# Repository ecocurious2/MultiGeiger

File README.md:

# MultiGeiger

Der MultiGeiger ist ein Messgerät für Radioaktivität. Er ist:

 * preiswert
 * ESP32-basiert
 * hat WiFi- bzw. WiFi/LoRa-Anbindung

**Multi**Geiger heißt er deshalb, weil das Gerät sehr viele Einsatz-Möglichkeiten hat:

 * Unterschiedliche Zählrohre - eine breite Palette von 400V-Zählrohren kann verwendet werden:

   - große Zählrohre, wie Si21g oder Si22g (wie wir es für die MultiGeiger-Messstation verwenden)
   - Mini-Zählrohr SBM21 (mit dem man sehr gut Hot-Spots aufspüren kann)

 * Unterschiedliche Verwendungen:

   - Multigeiger-Mess-Stationen für ein ODL-Mess-Netzwerk.
   - Mobiler Betrieb mit OLED-Anzeige.

# Ecocurious

Der MultiGeiger ist ein Projekt von Ecocurious, Deiner Umwelt-, Natur-  und Technik-Community, siehe https://ecocurious.de/projekte/multigeiger/.

Ziel ist es, ein Bürger-Messnetz für Radioaktivität in Deutschland aufzubauen.

Die MultiGeiger Hard- und Software hat Jürgen Böhringer konzipiert (http://www.boehri.de).

Reinhard/rexfue hat die Software und Platine weitergedacht und kümmert sich um die Einbindung der Sensoren in unsere Map https://ecocurious.de/multigeiger-karte/.

Wir haben die ersten Workshops gestartet, in denen Du die Bauteile und das Gehäuse mit unserer Unterstützung zusammenbauen kannst.

Workshop-Termine findest Du hier:
 * https://www.meetup.com/de-DE/Ecocurious-deine-Umwelt-Natur-und-Technik-Community/
 * https://ecocurious.de/events/

Klingt das interessant für Dich? Dann mach mit, herzliche Einladung!

## Installation
Hier in GitHub die neueste Release ( https://github.com/ecocurious/MultiGeiger/releases ) als Source code (zip) oder Source Code (tar.gz) herunterladen und entpacken.
Mit der Arduino-IDE in dem neuen Verzeichnis die Datei *multigeiger.ino* im Verzeichnis *multigeiger* öffnen.

Die Platine unterstützt zwei verschiedene Heltec-Bausteine, verschiedene Zählrohre und optional einen Temperatur/Luftdruck/Luftfeuchtigkeits-Sensor.
Die Software kann via Netzwerk Daten zu verschiedenen Services senden.

 * **Heltec WiFi Kit 32**
Diese MCU hat ein großes Display und WiFi.
Auf dem Board wird dieser Baustein in die längeren Buchsenleisten gesteckt.

 * **Heltec Wireless Stick**
Diese MCU hat ein sehr kleines Display, dafür aber zusätzlich zu WiFi noch LoRa.
Es wird in die kürzeren Buchsenleisten gesteckt.

Um die Heltec-Boards in der Arduino IDE auswählen zu können, muss https://raw.githubusercontent.com/espressif/arduino-esp32/gh-pages/package_esp32_dev_index.json in den Preferences unter Additional Boards Manager URLs hinzugefügt werden. Danach können unter Tools->Board->Boards Manager die ESP32 Boards (Name "esp32 by Espressif Systems")
installiert und anschließend unter Tools->Board das Heltec Board ausgewählt werden. Für **beide** Boards muss hier der **Heltec wireless Stick** ausgewählt werden. Die Software erkennt selbstständig, welches Board bestückt ist. Unter Tools muss noch **Flash size: "4MB(32Mb)"** und  **Partition Scheme: "Minimal SPIFFS (Large APPS with OTA)"** eingestellt werden.

Diverse Software-Einstellungen kann man über folgende Dateien machen (siehe Kommentare dort):

 * **./multigeiger/userdefines.h** (immer notwendig, ein Beispiel hierzu wird in userdefines-example.h mitgeliefert)
 * **./platformio.ini** (nur bei platformio, ein Beispiel hierzu wird in platformio-example.ini mitgeliefert)

Es werden alle externen Libraries benötigt, die in der Datei 
```
platformio-example.ini
```
unter dem Abschnitt 
```
lib-deps =
```
aufgelistet sind. Bitte jeweils die aktuellste Version über platform.io / Libraries installieren.

 **Achtung:** Wenn die Arduino-IDE verwendet wird, dann bitte prüfen, dass in der Datei project_config/lmic_project_config.h (in der obersten Ebene in dieser Library) unbedingt
```
die richtigen Configs eingestellt sind. Die Datei muss folgendermassen aussehen:
// project-specific definitions
#define CFG_eu868 1
//#define CFG_us915 1
//#define CFG_au921 1
//#define CFG_as923 1
// #define LMIC_COUNTRY_CODE LMIC_COUNTRY_CODE_JP	/* for as923-JP */
//#define CFG_in866 1
#define CFG_sx1276_radio 1
//#define LMIC_USE_INTERRUPTS
```
Die angegebenen Versionen der Libraries sind die Mindestanforderungen. Wir testen immer auch mit den neuesten Versionen, deshalb bitte immer die aktuellen Versionen installieren und verwenden.\
Falls der Compiler andere Libraries anmahnt, diese bitte in der Arduino IDE per *Sketch -> Include Library -> Manage Libraries ..* installieren.

## Ablauf nach dem Start
Das Gerät baut einen eigenen WLAN-Accesspoint (AP) auf. Die SSID des AP lautet **ESP32-xxxxxxxx**, wobei die xxx
die Chip-ID (bzw. die MAC-Adresse) des WLAN-Chips sind (Beispiel: **ESP32-51564452**).
**Bitte diese Nummer notieren, sie wird später noch gebraucht.**
Dieser Access-Point bleibt für 30sec aktiv. Danach versucht das Gerät, sich mit dem (früher) eingestellten WLAN
zu verbinden. Dieser Verbindungsversuch dauert ebenfalls 30sec. Kommt keine Verbindung zu Stande, wird wieder der
eigene AP für 30sec erzeugt. Wenn das WLAN nicht erreicht werden kann, läuft dieses Spiel endlos.
Solange keine Verbindung zum WLAN besteht, wird auf dem Display in der untersten Zeile ganz klein *connecting ...*
angezeigt. Diese Anzeige verschwindet, sobald eine WLAN-Verbindung hergestellt ist.

## Einstellung des WLAN
Wenn das Gerät den eigenen AP aufgebaut hat, verbindet man sich mit diesem. Entweder mit einem Handy oder einem PC o.ä..
Die Verbindung fragt nach einem Passwort, es lautet **ESP32Geiger**.
Ist die Verbindung mit dem Accesspoint hergestellt, hat man beliebig Zeit, die Daten einzugeben.
Es öffnet sich **automatisch** die Startseite des Gerätes. Es braucht also - in der Regel - nicht extra der Browser aufgerufen werden.
Falls die Startseite ausnahmsweise doch nicht erscheint, so muss mit dem Browser die Adresse **192.168.4.1** aufgerufen werden und nun erscheint die Startseite.
Dort findet man einen Link zur __configure page__ - dort drauf klicken und man kommt zur Einstellungsseite.

Diese hat die folgenden Zeilen:
 * Geiger accesspoint SSID\
 Dies ist die SSID des eingebauten APs und kann zwar geändert werden, sollte aber nicht! Der Sensor wird mit dieser Nummer bei sensor.community (früher: luftdaten.info) angemeldet. Wird sie geändert, muss eine neue Anmeldung erfolgen.
 * Geiger accesspoint password\
 Dies ist das Passwort für den eingebauten AP.\
 Dieses **MUSS** beim ersten Mal geändert werden. Es kann natürlich auch das gleiche Passwort **ESP32Geiger** wieder verwendet werden - wichtig ist nur, dass da was reingeschrieben wird und dass man das **nicht vergessen** darf.
 * WiFi client SSID\
 Hier muss die SSID des WLANs für den Netzwerk/Internet-Zugang eingegeben werden.
 * WiFi client password\
 Und hier das zugehörige Passwort.

Es wird empfohlen, beim WLAN das Gastnetz zu verwenden (falls ein solches existiert). Normalerweise wird das Gastnetz im Router vom normalen Netz abgeschottet und ist damit sicherer.

Ist alles eingegeben, kann man auf **Apply** drücken. Nun werden die eingestellten Daten übernommen und in das interne EEPROM gespeichert. Nun bitte **unbedingt** über **Abbrechen** diese Seite verlassen! Nur dann verlässt das Programm den Config-Mode und verbindet sich mit dem heimischen WLAN. Wenn es kein **Abbrechen** gibt, dann wieder zurück in die WLAN-Einstellungen des Gerätes gehen und da dann das normale Heim-Netzwerk wieder einstellen.

**ACHTUNG ACHTUNG**\
**Beim Update auf die Version 1.13 müssen die WLAN-Daten noch einmal neu eingegeben werden**. Bei zukünftigen Versionen wird das nicht mehr nötig sein.

Weiter können über die Einstell-Seite einige verschiedene Definitionen festgelegt werden:

* Start-Melodie, Lautsprecher-Tick, LED-Tick und Anzeige jeweils an oder aus
* Senden zu sensor.community oder/und zu madavi.de
* bei LoRa-Hardware können hier auch die LoRa-Kenngrößen (DEVEUI, APPEUI und APPKEY) eingegeben werden.

Am Ende der Einstellungsseite gibt es einen Link __Firmware update__ - hiermit kann man die Software auf dem MultiGeiger aktualisieren.
Man braucht dazu die .bin-Datei, wählt diese dann über **Browse...** aus und klickt zum Aktualisieren auf **Update**.
Danach dauert es ca. 30s für das Hochladen und Flashen der Datei.

Der Browser zeigt dann (hoffentlich) **Update Success! Rebooting...** an, der MultiGeiger startet dann neu und ab dann ist die neue
Firmware aktiv.

Erscheint **Update error: ...**, dann hat das Update nicht geklappt - es ist dann die seitherige Firmware weiter aktiv.

### Aufruf aus dem WLAN ###
Die Einstellseite kann zu jeder Zeit aus dem eigenen WLAN heraus aufgerufen werden. Dazu 
wird in der Adresszeile des Browsers http://esp32-xxxxxxx eingegeben. Hier ist xxxxxxx wieder die Chip-ID (siehe oben, Beispiel: **http://esp32-51564452**). Sollte es mit diesem Hostnamen nicht klappen, dann muss die IP-Adresse des Geigerzählers verwendet werden, diese kann aus dem Router ausgelesen werden.
Es erscheint zunächt eine Login-Seite.
Hier ist als Username **admin** und als Passwort das **Geiger accesspoint password** von oben einzugeben. Dann erscheint die gleiche Einstellseite wie oben beschrieben.

## Server
Es werden jeweils einen Messzyklus lang die Impulse gezählt und dann die "Counts per Minute" (cpm) berechnet.
Jeweils nach diesem Zyklus werden die Daten zu den Servern bei *sensor.community* und bei *madavi.de* gesendet.

Bei *sensor.community* werden die Daten gespeichert und stehen am nächsten Tag zum Abruf als CSV-Datei bereit:
http://archive.sensor.community/DATE/DATE_radiation_si22g_sensor_SID.csv
wobei DATE = Datum im Format YYYY-MM-DD ist (beides mal gleich) und SID die Sensornummer des Sensors (**nicht** die ChipID). Bei anderen Sensoren ist der Zählrohr-Name **si22g** durch den entsprechenden Namen zu ersetzen (z.B.: sbm-20 oder sbm-19) 

Bei *madavi* werden die Daten in einer RRD-Datenbank abgelegt und können direkt aktuell als Grafik über diesen Link betrachtet werden:
https://www.madavi.de/sensor/graph.php?sensor=esp32-CHIPID-si22g
Hier ist dann CHIPID die ChipId (also die Ziffern der SSID des internen Accesspoints).

Während der Übertragung der Daten zu den Servern wird in der Statuszeile (unterste Zeile) des Displays kurz der Name des Servers eingeblendet.

## Anmeldung bei sensor.community (luftdaten.info)
Damit die Daten, die der Sensor nach sensor.community schickt, von dem Server auch angenommen werden, muss man sich dort anmelden. Das geschieht über die Seite https://meine.luftdaten.info.
Zuerst über den *Registrieren*-Knopf einen Account anlegen. Dann damit über *Login* einloggen und *Neuen Sensor registrieren* anklicken.
Dann das Formular ausfüllen:
 * Erste Zeile, Sensor ID:\
 Hier die Nummer (nur die Zahlen) der SSID des Sensors eingeben (z.B. bei dem Sensor ESP-51564452 also dann nur 51564452 eingeben)
 * Zweite Zeile, Sensor Board:\
 Hier *esp32* auswählen (über die kleinen Pfeile rechts)
 * Basisinformation:\
 Hier die Adresse eingeben (mit dem Land!). Der interne Name des Sensors kann beliebig vergeben werden, muss aber eingegeben werden. Bitte den Haken bei **Indoor-Sensor** setzen, so lange der Sensor wirklich innen ist.
 * Zusätzliche Informationen:\
 Kann freigelassen werden, darf aber auch ausgefüllt werden.
 * Hardware-Konfiguration:\
 Hier als Sensor-Typ den Eintrag **Radiation Si22G** (oder ggf. entsprechend) auswählen. Für den zweiten Sensor kann DHT22 stehen bleiben, das ist für uns irrelevant.
 * Position\
 Hier bitte die Koordinaten eingeben, so genau wie möglich (oder über den rechten Knopf die Koordinaten rechnen lassen). Dies wird benötigt, um den Sensor später auf der Karte anzeigen zu können.

 Nun mit *Einstellungen speichern* das Ganze beenden. Dann auf der Übersichts-Seite bei diesem Sensor auf *Daten* klicken. Nun steht hinter *Sensor ID* die ID des Sensors. Diese bitte merken: sie wird für die Abfrage bei sensor.community bzw. bei der Anzeige auf https://multigeiger.citysensor.de benötigt.
 
## LoRa-Interface
Um den Multigeiger an TTN ("The Things Network") anzubinden, sind ein paar vorbereitende Schritte durchzuführen:

* Anlegen des TTN-Devices bei *The Things Network*
* Übernehmen der Parameter in den Multigeiger
* Anmelden bei *sensor.community* (ehemals luftdaten.info)
* HTTP-Integration

### Anlegen eines TTN-Devices
Das Gerät muss bei TTN (The Things Network) angemeldet werden. Dazu muss zuerst (falls noch nicht vorhanden) ein Account bei TTN angelegt werden.

#### Account anlegen
Über <https://account.thethingsnetwork.org/register> auf die Webseite zum Account anlegen gehen. Hier dann einen **USERNAME** vergeben, die **EMAIL ADRESSE** eintragen und auch ein **PASSWORD** vergeben. Dann rechts unten über **Create account** den Account anlegen. Danach kann man sich mit den neuen Daten an der Console anmelden (<https://account.thethingsnetwork.org/users/login>).

#### Applikation anlegen
Ist man eingelogged, wird über **APPLICATIONS** und **add applications** die neue Applikation angelegt. Folgende Felder müssen ausgefüllt werden:

* **Application ID:**\
Eine beliebige Bezeichnung für diese Applikation, die darf es aber in dem Netzwerk noch nicht geben (also z.B.: geiger_20200205)
* **Description:**\
Hier kann eine beliebige Beschreibung der Apllikation eingegeben werden.
* **Application EUI:**\
Bleibt frei, die Nummer wird vom TTN-System erzeugt.
* **Handler registration:**\
Der vorausgefüllte Wert (ttn-handler-eu) ist schon richtig und bleibt stehen.

Nun mit **Add application** rechts unten die Apllikation hinzufügen.

#### Device anlegen
Zuletzt muss noch das Device angelegt werden. Dazu in der Übersicht der Applikationen die gerade neu angelegte Applikation auswählen (klicken). Hier dann im mittleren Bereich bei **DEVICES** das Anlegen eines neuen Devices über **register device** starten. Folgende Felder müssen ausgefüllt werden:

* **Device ID:**\
Ein beliebiger Name für das Device. Er muss innerhalb der Applikation eindeutig sein (also z.B.: geiger_01) und nur aus Kleinbuchstaben bestehen.
* **Device EUI:**\
Einmal auf das Symbol ganz links an der Zeile klicken, dann erscheint der Text, dass diese Nummer vom System erzeugt wird. Wir müssen sonst nichts weiter eingeben.
* **App Key:**\
Keine Eingabe nötig
* **App EUI:**\
Bleibt so stehen

Nun rechts unten auf **Register**. Nun ist auch das Device angelegt.

### Übernahme der LoRa-Parameter 
Die LoRa-Parameter müssen noch in das Programm übernommen werden.\
Dazu muss die Konfigurations-Webseite des Geigerzählers aufgerufen werden. Weiter oben ist erklärt, wie die Konfigurations-Seite zu erreichen ist (*Einstellung des WLAN* und *Aufruf aus dem WLAN*))

Nun auf der Konfigurations-Seite durch die Konfiguration gehen bis die Einstellung der LoRa-Parameter angezeigt wird. Nun die 3 Werte (**APPEUI, DEVEUI, APPKEY**) aus der TTN-Console (siehe oben) entnehmen und hier dann eintragen. In der TTN-Console auf das Device gehen, das oben angelegt wurde. Hier sind die 3 Werte zu finden. Es müssen die HEX-Werte **ohne** Leerzeichen eingegeben werden, und zwar so, wie sie in der TTN-Console erscheinen.
Beispiel:\
in der TTN-Console steht

```
Device EUI  00 D0 C0 00 C3 19 7C E8
```
Dann muss folgendes eingeben werden:

```
00D0C000C3197CE8
```
Dies gilt genauso ebenso für die **APPEUI** und den **APPKEY** .

### Anmelden bei sensor.community (ehem. luftdaten.info)
Wenn der Multigeiger seine Daten über TTN auch an *sensor.community* weitergeben soll, muss er dort angemeldet werden.
Die Anmeldung ist ziemlich ähnlich wie oben schon beschrieben. Hier werden nur die Änderungen erläutert (gesamten Ablauf bitte oben nachlesen).

 * Sensor ID:\
 Hier den hinteren Teil der DEVEUI eingeben (wenn also - siehe oben - die DEVEUI *00 D0 C0 00 C3 19 7C E8* heißt, sind die hinteren 4 Byte ( also *C3197CE8*) in dezimal umgerechnet ( also hier 3273227496 ) einzugeben.
 * Sensor Board:\
 Hier **TTN** auswählen (über die kleinen Pfeile rechts).

### HTTP-Integration
Um die Daten von TTN an *sensor.community* zu bekommen, muss noch die HTTP-Integration bei TTN eingestellt werden.\
In der TTN-Console *Applications* anklicken und dann die Applikation des Geigerzählers (z.B. *geiger_20200205*) anklicken. Dann rechts oben in der Leiste mit *Overview*, *Devices*, *Payload Formats*, *Integrations*, *Data*, *Settings* das **Integrations** anklicken. Hier dann über **add integration** die **HTTP Integration** auswählen.

Nun die angezeigten Felder ausfüllen:\
 **Process ID:**\
 	Hier einen beliebigen Namen für diese Integration vergeben\
 **Access Key:**\
 	Hier einmal rein klicken und den *default key* auswählen\
 **URL:**\
 	Hier nun die URL zum ttn2luft-Programm eingeben: <https://ttn2luft.citysensor.de>\
 **Method:**\
 	da steht schon *POST*, das lassen\
 **Authorization:**\
 	bleibt leer\
 **Custom Header Name:**\
 	hier kommt der Text **X-SSID** rein\
 **Custom Header value:**\
 	und da dann die SSID des Sensors (also die Nummer, die man bei der Anmeldung bei sensor.community erhalten hat, *NICHT* die Chip-ID).

Dann rechts unten auf **Add integration** klicken. Das war's dann.\
Und so etwa sieht das dann ausgefüllt aus:\

### TTN-Payload (Beispiel)
Um in der TTN-Console nicht nur die Datenbytes sondern lesbare Werte zu sehen, kann ein kleines Script als payload-Decoder eingefügt werden.\
Auf der *The Things Network* Webseite einloggen, über **Applications** die oben angelegte Application suchen und dann anklicken. Hier in der Menü-Zeile den Tab **Payload Formats** auswählen. Dann den folgenden Code in das Feld einfügen (den vorhandenen Code überschreiben):

```
function Decoder(bytes, port) {
  // Decode an uplink message from a buffer
  // (array) of bytes to an object of fields.
  var decoded = {};
  if(port == 1) {
  decoded.counts = ((bytes[0]*256 + bytes[1]) * 256 + bytes[2]) * 256  + bytes[3];
  decoded.sample_time = (bytes[4] * 256 + bytes[5]) * 256 + bytes[6];
  decoded.tube = bytes[9];
  var minor = (bytes[7]&0xF)+(bytes[8]>>4) ;
  decoded.sw_version="" + (bytes[7]>>4) + "." + minor + "." + (bytes[8]&0xF);
  }
  if (port === 2) {
    decoded.temp = ((bytes[0] * 256 + bytes[1]) / 10) + "°C";
    decoded.humi = bytes[2] / 2 + "%";
    decoded.press = ((bytes[3] * 256 + bytes[4]) / 10) + "hPa";
  }
  return decoded;
}
```

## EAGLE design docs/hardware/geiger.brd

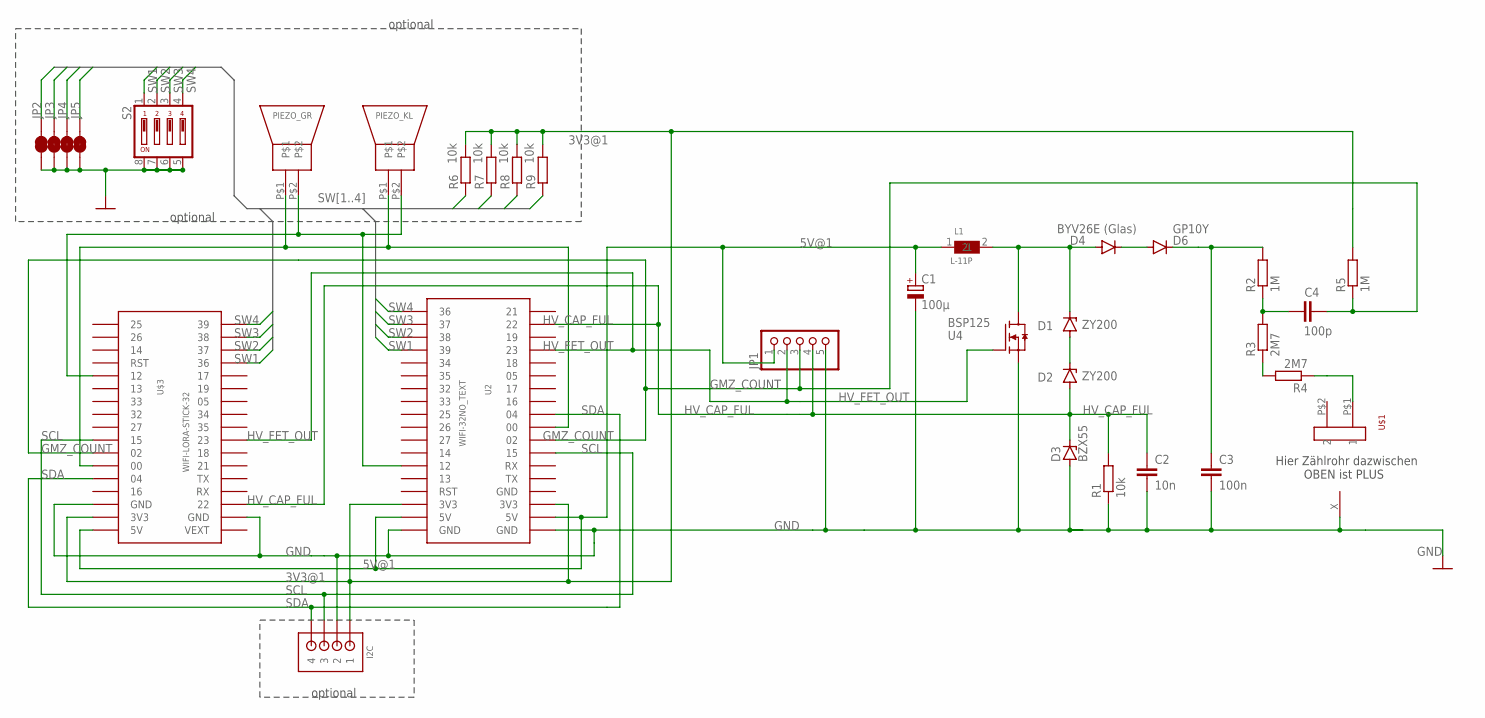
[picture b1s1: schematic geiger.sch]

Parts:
C1: 100µ; E2-5
C2: 10n; C050-035X075
C3: 100n; C150-072X183
C4: 100p; C050-045X075
D1, D2: ZY200; DO41Z10
D3: BZX55; DO35Z10
D4: BYV26E (Glas); DO41-10
D6: GP10Y; DO41-10
I2C: B4B-ZRSIDE_ENTRY; S4B-ZR
JP1: PINHD-1X5; 1X05
JP2: Jumper; SMT-JUMPER_2_NC_TRACE_NO-SILK
JP3, JP4, JP5: JUMPER-SMT_2_NC_TRACE_NO-SILK; SMT-JUMPER_2_NC_TRACE_NO-SILK
L1: L-11P
PIEZO_GR: PIEPSER_BIG
PIEZO_KL: PIEPSER
R1: 10k; 0207/10
R2, R5: 1M; 0207/10
R3, R4: 2M7; 0207/10
R6, R7, R8, R9: 10k; M0805
S2: DIP04YL
U2: WIFI-32NO_TEXT; 2.54MM_2X18_NOLORA_NOTEXT
U4: BSP125; SOT223
U$1: FUSE_HOLDER
U$3: WIFI-LORA-STICK-32; 2.54MM_2X18_STICK_NO_TEXT
U$5: ONE_PAD

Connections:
3V3@1: I2C.1, R5.2, R6.2, R7.2, R8.2, R9.2, U2.P$3 (3V3), U2.P$34 (3V3), U$3.P$33 (3V3)
5V@1: C1.+, JP1.1, L1.1, U2.P$2 (5V), U2.P$35 (5V), U$3.P$34 (5V)
GMZ_COUNT: C4.2, JP1.3, R5.1, U2.P$29 (02), U$3.P$28 (02)
GND: C1.-, C2.2, C3.2, D3.A, I2C.2, JP1.5, JP2.1, JP3.1, JP4.1, JP5.1, R1.1, S2.5, S2.6, S2.7, S2.8, U2.P$1 (GND), U2.P$36 (GND), U4.3 (S), U$3.P$2 (GND), U$3.P$32 (GND), U$5.X
HV_CAP_FUL: C2.1, D2.A, D3.C, JP1.4, R1.2, U2.P$20 (22), U$3.P$3 (22)
HV_FET_OUT: JP1.2, U2.P$22 (23), U4.1 (G), U$3.P$8 (23)
unnamed: D1.A, D2.C
unnamed: D1.C, D4.A, L1.2, U4.2 (D), U4.4 (D)
unnamed: C3.1, D6.C, R2.2
unnamed: R4.1, U$1.P$1 (1)
unnamed: R3.1, R4.2
unnamed: C4.1, R2.1, R3.2
unnamed: D4.C, D6.A
unnamed: PIEZO_GR.P$2, PIEZO_KL.P$2, U2.P$6 (12), U$3.P$22 (12)
unnamed: PIEZO_GR.P$1, PIEZO_KL.P$1, U2.P$28 (00), U$3.P$29 (00)
SCL: I2C.3, U2.P$30 (15), U$3.P$27 (15)
SDA: I2C.4, U2.P$27 (04), U$3.P$30 (04)
SW1: JP5.2, R6.1, S2.1, U2.P$15 (39), U$3.P$14 (36)
SW2: JP4.2, R7.1, S2.2, U2.P$16 (38), U$3.P$15 (37)
SW3: JP3.2, R8.1, S2.3, U2.P$17 (37), U$3.P$16 (38)
SW4: JP2.2, R9.1, S2.4, U2.P$18 (36), U$3.P$17 (39)

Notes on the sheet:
Hier Zählrohr dazwischen OBEN ist PLUS
optional

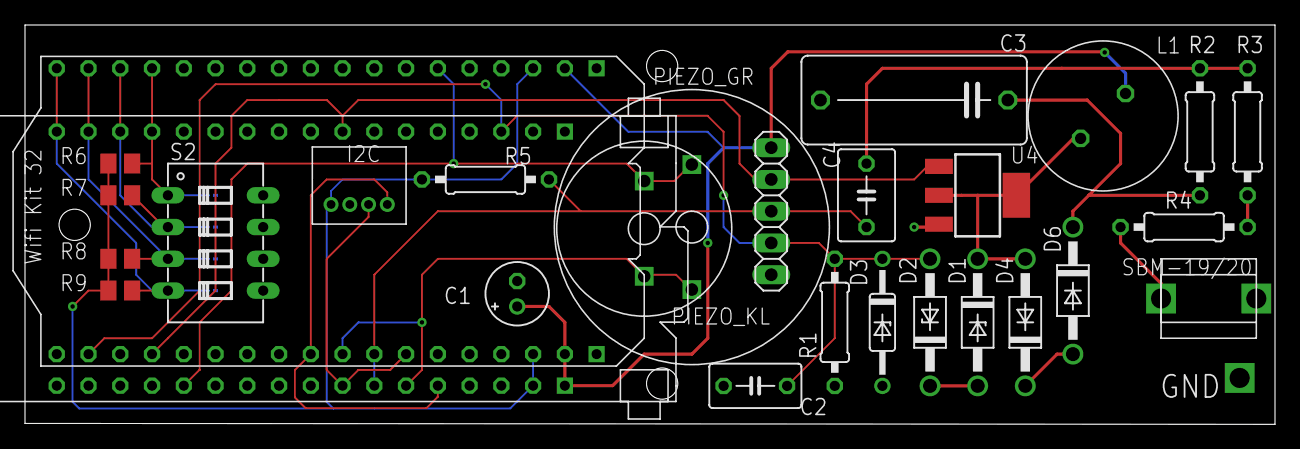
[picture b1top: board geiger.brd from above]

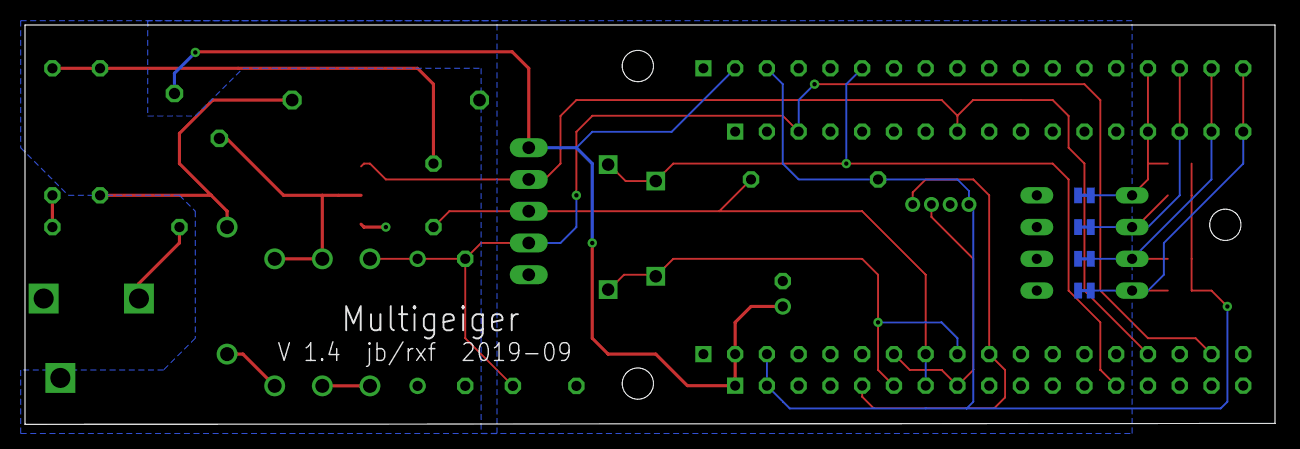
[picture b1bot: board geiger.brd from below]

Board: 2 copper layers, 100.0 x 31.9 mm, 33 parts (4 on the bottom side), 21 nets.

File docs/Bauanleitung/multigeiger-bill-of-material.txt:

TEIL	ANZAHL 	BESCHREIBUNG	Artikelbezeichnung	LINK
T1	1	N-MOS-Transistor BSP125,	BSP125H6433XTMA1	https://www.digikey.ch/product-detail/de/BSP125H6433XTMA1/BS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
R1	1	kOhm Widerstand, braun-schwarz-orange-gold, Kohleschicht, 0411, 500 mW, 5%	z.B. RD12JN103T52	https://www.reichelt.de/ch/de/widerstand-kohleschicht-10-koh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
R2, R5	2	1,0 Mohm Widerstand, braun-schwarz-grün-gold, Kohleschicht, 0207, 250 mW, 5%	z.B. CFR-25JT-52-1M	https://www.reichelt.de/ch/de/widerstand-kohleschicht-1-0-mo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
R3, R4	2	4,7 Mohm Widerstand, gelb-violett-grün-gold,  Kohleschicht, 0207, 250 mW, 5%	z.B. CFR-25JT-52-4M7	https://www.reichelt.de/ch/de/widerstand-kohleschicht-4-7-mo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
D1, D2	2	Z-Diode, ZY 200	ZY200 oder BZX85C200	https://www.reichelt.de/ch/de/zenerdiode-200-v-2-w-do-41-zy-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 oder https://www.reichelt.de/ch/de/zenerdiode-200-v-2-w-do-204al-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
D3	1	Z-Diode, 3,3 V, 0,5 W, DO-35	BZX55C3V3	https://www.reichelt.de/ch/de/zenerdiode-3-3-v-0-5-w-do-35-b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
D4	1	Gleichrichterdiode, 1000 V, 1 A, SOD-57	BYV26E	https://www.reichelt.de/ch/de/gleichrichterdiode-1000-v-1-a-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
D6	1	Gleichrichterdiode GP10Y, 1.6 kV, 1 A	GP10Y-E3/54	https://www.digikey.ch/product-detail/de/GP10Y-E3%2f54/GP10Y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
C1	1	ELKO Elektrolytkondensator 100 uF, 16 V	SKR101M1CE11VM	https://www.reichelt.de/ch/de/elko-radial-100-f-16-v-rm-2-5-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
C2	1	Folienkondensator, 10nF, 100V, FKP2-100 10N, "0.01  100-"	FKP2D021001I00HSSD	https://www.reichelt.de/ch/de/folienkondensator-10nf-100v-rm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
C3	1	Folienkondensator, 100nF, 630V, MKP4-630 100N, "0.1  630-"	MKP4J031004D00KSSD	https://www.reichelt.de/ch/de/folienkondensator-100nf-630v-r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
C4	1	Folienkondensator, 100pF, 1000V, FKP2-1000 100P, "100/1000-"	FKP2O101001D00HSSD	https://www.reichelt.de/ch/de/folienkondensator-100pf-1000v-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
L1	1	Spule, 150 uH, "154J"	11P-154J-50	https://www.reichelt.de/ch/de/stehende-induktivitaet-11p-fer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
Pz1	1	Piezo-Lautsprecher	AL-60SP05	https://www.reichelt.de/ch/de/elektromagnetischer-summer-sum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
X1, X2	2	Zählrohrhalter		
	1	Zählrohr SBM-20, SBM-19 oder Si22G, (andere möglich, wobei Umrechnungsfaktor muss in Firmware angepasst werden muss)	 SBM-20, SBM-19 oder Si22G	diverse, z.B. ebay, häufig russische oder ukranische Verkäufer
	2	Buchsenleiste, Fassung für Microcontroler-Modul

Optional Parts
TEIL	ANZAHL 	BESCHREIBUNG	Artikelbezeichnung	LINK
S2	1	DIP-Schalter, 4-polig, Piano-Dip Ausführung	DP 04	https://www.reichelt.de/index.html?ACTION=446&LA=0&nbc=1&q=dp%2004

R6, R7, R8, R9	4	10k Ohm SMD Widerstand, 0805	RND 0805 1 10K	https://www.reichelt.de/smd-widerstand-0805-10-kohm-125-mw-1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

I2C	1	Stiftleiste Micro JST 1.5mm, ZH 4-Pin,

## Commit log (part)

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2020-02-10 astyle: unpad-paren pad-header
2020-02-10 automatic formatting
2020-02-11 new log(level, format, ...) function, fixes #161
    - printf-style call
    - only outputs for level >= log_level
    - levels: DEBUG, INFO, WARNING, ERROR
    - internally prepends "GEIGER: " to differentiate our output from other
    - adds correct line endings by using Serial.println()
2020-02-11 add DEFAULT_LOG_LEVEL and NOLOG level
2020-02-11 rename example .travis.yml file
2020-02-11 travis: show astyle version
2020-02-11 platformio on travis has issues with the U8g2 entry
    try if multi-line and some addtl. blanks help.
    error message:
    LDF: Library Dependency Finder -> http://bit.ly/configure-pio-ldf
    LDF Modes: Finder ~ chain, Compatibility ~ soft
    Looking for U8g2@> library in registry
    Warning! Library `{'name': 'U8g2@>', 'requirements': '>=1.0.2,'}` has
2020-02-11 improve development docs
2020-02-12 New 5V Power Supply (including adapters and cables)
    ... based ot TWs Idea
2020-02-14 use bump2version tool for version bumps, fixes #169
    derive everything from VERSION_STR, kill VERSION_DATE
    bump2version can only deal with the string, not with dates.
    the lora_software_version value is now computed from the string.
    the date of a release can be looked up in the changelog (or in git).
    for the version string, we display as much of it as possible
    on the specific display (by just truncating it).
2020-02-17 rename time2hvpulse -> hvpulse_timestamp
    that variable contains the timestamp in ms of the most recent
    HV pulse - it is NOT the "time to (the next) hv pulse".
2020-02-20 move IotWebConfig related code to webconf.*, see #159
2020-02-20 move sound/speaker/tick related code to speaker.*, see #159
2020-02-20 moved bme280 related code to thp_sensor.*, see #159
2020-02-20 refactor display code for bigger display
2020-02-20 refactor speaker code
    reduce code duplication, simplify.
2020-02-20 loraWan: fix unhandled cases in switch-statement
    not sure this is the most correct way to deal with that case,
    but i did not change behaviour, just fixed the compiler warning:
    loraWan.cpp:299:18: error: enumeration value 'TX_STATUS_ENDING_ERROR'
    not handled in switch [-Werror=switch]
    switch ( txStatus ) {
    same for TX_STATUS_TIMEOUT.
2020-02-20 transmission: actually readable json generation
2020-02-20 fix preprocessing, standard include ifndef-define-endif dance
2020-02-21 remove bme/BME from variable names, fixes #210
2020-02-21 loraWan: remove exclusion from .astylerc
    this is NOT 3rd party code, but our lora sending code.
2020-02-22 directly initialize afterStartTime to desired value
    remove the unneeded first init.
2020-02-22 remove unneeded global variables
    these were just assigned once from the userdefines constants,
    so we can just directly use these.
2020-02-22 rename toSendTime -> transmission_timestamp
2020-02-22 simplify one-minute log calculations
2020-02-22 cosmetic: reorder / group together the variable definitions
2020-02-22 remove some superfluous comments
    comments are only useful if they really add information that
    can not be easily seen anyway. otherwise they are just overhead.
2020-02-22 replace long license legalese by a shorter version.
2020-02-23 exclude all of .vscode
2020-02-24 fix astyle complaints
2020-02-25 fixed typo added explanation for XPIN 0
2020-03-07 Unnecessary externs removed
2020-03-12 fixed some oddities - restored #defines in userdefines-example.h
2020-03-25 thp_sensor: use less globals
2020-03-25 configuration form: better separator texts
2020-03-26 webconf: boolean format/parse functions
2020-04-14 fixed typos, restored LMIC conf
2020-04-14 Bump version: 1.12.1-dev → 1.13.0
2020-04-16 Name of boards manager fixed
2020-04-19 Passworterläuterungen
2020-05-03 do not use test pin except when enabled, see #220
    having a test pin that is toggled while the ISR for GM pulse counting
    is active is nice for hardware debugging (e.g. with oscilloscope), but
    not needed for production use.
    by using a preprocessor #if block, the 2 digitalWrite() calls are not
    done in production, which likely speeds up the ISR processing quite a
    bit.
2020-05-03 separate THP measurement from unrelated code
2020-05-04 changed version numbers for libraries
2020-05-04 removed "Fixme" and more
2020-05-04 use persistent per-server HTTPClient instances
    this prepares for keeping connections open,
    which is good for speed, esp. for https speed.
2020-05-04 add https support for sending data
2020-05-05 update display.cpp - new font (u8x8 uses 8px width anyway), prepare for BLE connectivity, changed symbol CPS to CPM
2020-05-06 update display.cpp - small changes from Thomas' suggestions
2020-05-09 display.cpp adaptions also for Lora board
2020-05-09 timer interrupt driven, adaptive hv charging, fixes #192
2020-05-11 Adde LoRa descriotion
2020-05-11 fixed typos
2020-05-11 check for http transmission errors, update status, fixes #265
2020-05-11 fix "time in between" init
    this is a time **difference** not an absolute timestamp.
2020-05-12 timer driven audio/led sequencer, PWM sound, fixes #35
    hardware PWM (with complementary outputs) for sound (ticks and tones).
    timer driven audio sequencer, supports tones, speaker and LED "ticks".
    can be fed with a list of (frequency, volume, led, duration) integers.
    geiger mueller "tick" at 5000Hz, debug "tock" at 1000Hz.
2020-05-12 add bme680 library for basic THP readout of BME680
    add bme680 library for basic THP readout of BME680
    small fixes, use type_thp instead of have_thp, updated README
    changed BME init sequence
    fix astyle issues
2020-05-13 toilet -> custom server, add comments about toilet usage, fixes #214
2020-05-13 docs: add usage chapter, description of OLED display, fixes #264 (#284)
    add usage chapter, description of OLED display, fixes #264
2020-05-13 status display: keep showing transmission errors
    in case of some unsuccessful transmission attempt, the error code was
    only shown for a short time and then replaced by idle status again.
    fixed, now the error code is shown until the transmission is retried.
    also removed some unneeded status display related code for BT and LoRa,
    the initial state is "NODISPLAY" anyway.
2020-05-13 update CHANGES (#283)
    update CHANGES
2020-05-13 remove unused #defines
2020-05-14 show lora error on status display
2020-05-14 display: simplify formatting for big display
    prepare formatted time, then do final formatting / output.
2020-05-14 display: move time formatting to separate function
2020-05-14 removed meeting notes, fixes #294
2020-05-15 changed wifistatus to wifi_status
2020-05-15 disable ticking before save/flash, fixes #304, fixes #305
2020-05-16 Bump version: 1.14.0 → 1.15.0-dev
2020-05-20 fine-tuning: center, underline, snake_case in display.cpp
2020-05-21 Aufbauanleitung 2019_13_09
2020-05-21 add xkcd about radiation doses to FAQ, fixes #310
2020-05-21 suggestions from review
    fix astyle issues
    separate disable_ble() function
2020-05-21 add locales (only "de" for now)
    translation happens on transifex, this is:
    - a backup
    - likely needed for readthedocs also
2020-05-21 docs: how to update docs translations
2020-05-22 gitignore *.mo
2020-05-22 comment added
2020-05-22 more trailing spaces removed
2020-05-22 swap new and old readme
2020-05-22 BLE updated in status documentation
2020-05-22 remove "Version:" from start screen, fixes #335
2020-05-22 added remark about possible slow reaction times from BLE
2020-05-22 more style fixes
2020-05-22 BLE: naming consistency (cosmetic), fixes #315
2020-05-23 docs: add links to legacy docs, add hints
2020-05-23 docs: document dip switch usage, fixes #128
2020-05-25 changed 'not configured / enabled' to 'not configured, not enabled'
2020-11-23 Fixed typo in URL
2020-12-29 add github ci workflow
    for now, just the astyle checker.
2020-12-29 fix typo in translation workflow docs
2020-12-31 update translations
2021-01-10 Update resources.rst
    Added supported counter tubes
2021-01-13 unnecessary 'parse_bool' deleted
2021-03-01 Add LMIC polling from loop()
2021-03-07 docs: talk about transifex in development docs
2021-03-07 corrected indents and items
2021-03-07 Fix for gettext issues
2021-03-07 Moved images folder to docs/source folder #345
2021-03-07 Spelling changes in the assembly guide
2021-03-09 Optimized layout for epub export and changed line breaks
    Changed line breaks in source file to make future diffs easier.
2021-03-20 reorder TOC, fixes #387
2021-03-20 AssemblyGuide TOC entry -> Assembly
2021-03-20 TOC: call both the generic and lora parts "SETUP"
2021-03-20 transifex: add resource for "about"
2021-03-21 remove 404 links to deleted docs
    these docs were integrated into the *.rst docs and then deleted.
2021-03-21 speaker: init "duty_mode" member in MCPWM config
    I've seen a traceback pointing to an MCPWM issue
    and found that this member of the struct has not been
    initialized yet.
2021-03-21 Bump version: 1.15.0-dev → 1.15.0
2021-03-23 update developer docs: bump master branch version to -dev after release
2021-03-25 cosmetic: don't touch LED in pauses between melody notes
2021-04-02 Changed switch numbering, fixes #349
2021-04-23 no iotwebconf version number in platform.ini
2021-05-02 Fix Adafruit BME680 #macro name change
2021-05-04 BLE via NimBLE-Arduino lib
    astyle issues try #1
    astyle issues try 2
    astyle issues try 3 - unary operator position
    astyle issues try 4 - if<space>(condition)
2021-05-06 Fix sensor.community domain
2021-05-10 uses iotwebconf 3.0.2
2021-05-10 fix BT docs reST formatting
2021-05-13 Bump version: 1.16.0-dev → 1.15.1
2021-05-15 init WS2812 LED from main setup(), more logging
2021-05-15 remove userdefines.h based LED configuration
    needs to be done by iotwebconf config item.
2021-06-18 remove unused ntp/time related code, fixes #429
2021-06-18 use THP: prefix for temperature, humidity, pressure log output
2021-06-18 lora: replace event_log() by log()
    as log() now always adds a timestamp, there is no need for a custom event_log()
    that just adds a timestamp any more.
2021-06-18 geiger transmit: remove extra timestamp output
2021-06-18 fixup: remove utf-8 encoded degree char disturbing formatted output
    ° (degree) char is encoded as 2 bytes, so C thinks it takes 2 char cells on the screen.
    but it only renders as 1 char cell wide, so everything is rendered 1 position too far left.
2021-06-18 astyle fixes
2021-07-03 sequencer fix: avoid accessing global outside of mutex block
    isr_sequence is a global variable and we must not access it without holding the mux_audio mutex.
    fix: use p, it is a local variable and gets the value of isr_sequence WHILE holding the mutex.
    thanks to @t-pi for discovering this issue!
2021-07-04 local alarm IotWebConf for local alarm
2021-07-05 small fixes (wording, consistent alarm SOUND, ...) from TW review
2021-08-15 Bump version: 1.16.0-dev → 1.16.0
2021-09-10 fix uptime display - casting brackets
2021-09-25 Send data or alerts to Telegram Messenger chat Small changes to userdefines stylecheck fixes stylecheck fix 2
2021-10-03 Messenger and telegram config via IotWebConf
2022-02-06 Refactor GMC data processing
2022-02-12 send env data via BLE
2022-02-12 Added linked picture for I2C documentation
2022-02-20 astyle fix
2022-02-26 Removed the picture, fixed typos
2022-04-07 translations completed various smaller fixes
2022-04-08 README_FORK.md format fixes, pictures added
2022-05-16 new tube
2022-06-26 update .gitignore
    ignore multigeiger.ino.cpp
2023-05-22 Update setup_lora.rst
    Changes made according to TW's suggestions

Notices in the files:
parts and their libraries:
SparkFun-Jumpers: Licensing: Creative Commons ShareAlike 4.0 International - https://creativecommons.org/licenses/by-sa/4.0
